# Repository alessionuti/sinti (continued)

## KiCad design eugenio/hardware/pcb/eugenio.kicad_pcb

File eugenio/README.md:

# Eugenio
## Euclidean sequencer
See `manual/` for full documentation.

### Acknowledgements
Inspired by:
- [Tombola](https://modwiggler.com/forum/viewtopic.php?t=45485)'s Euclidean Polyrhythm Generator
- [TimMJN](https://github.com/TimMJN/Arduino-Euclidean-Rhythm-Generator)'s Arduino Euclidean Rhythm Generator

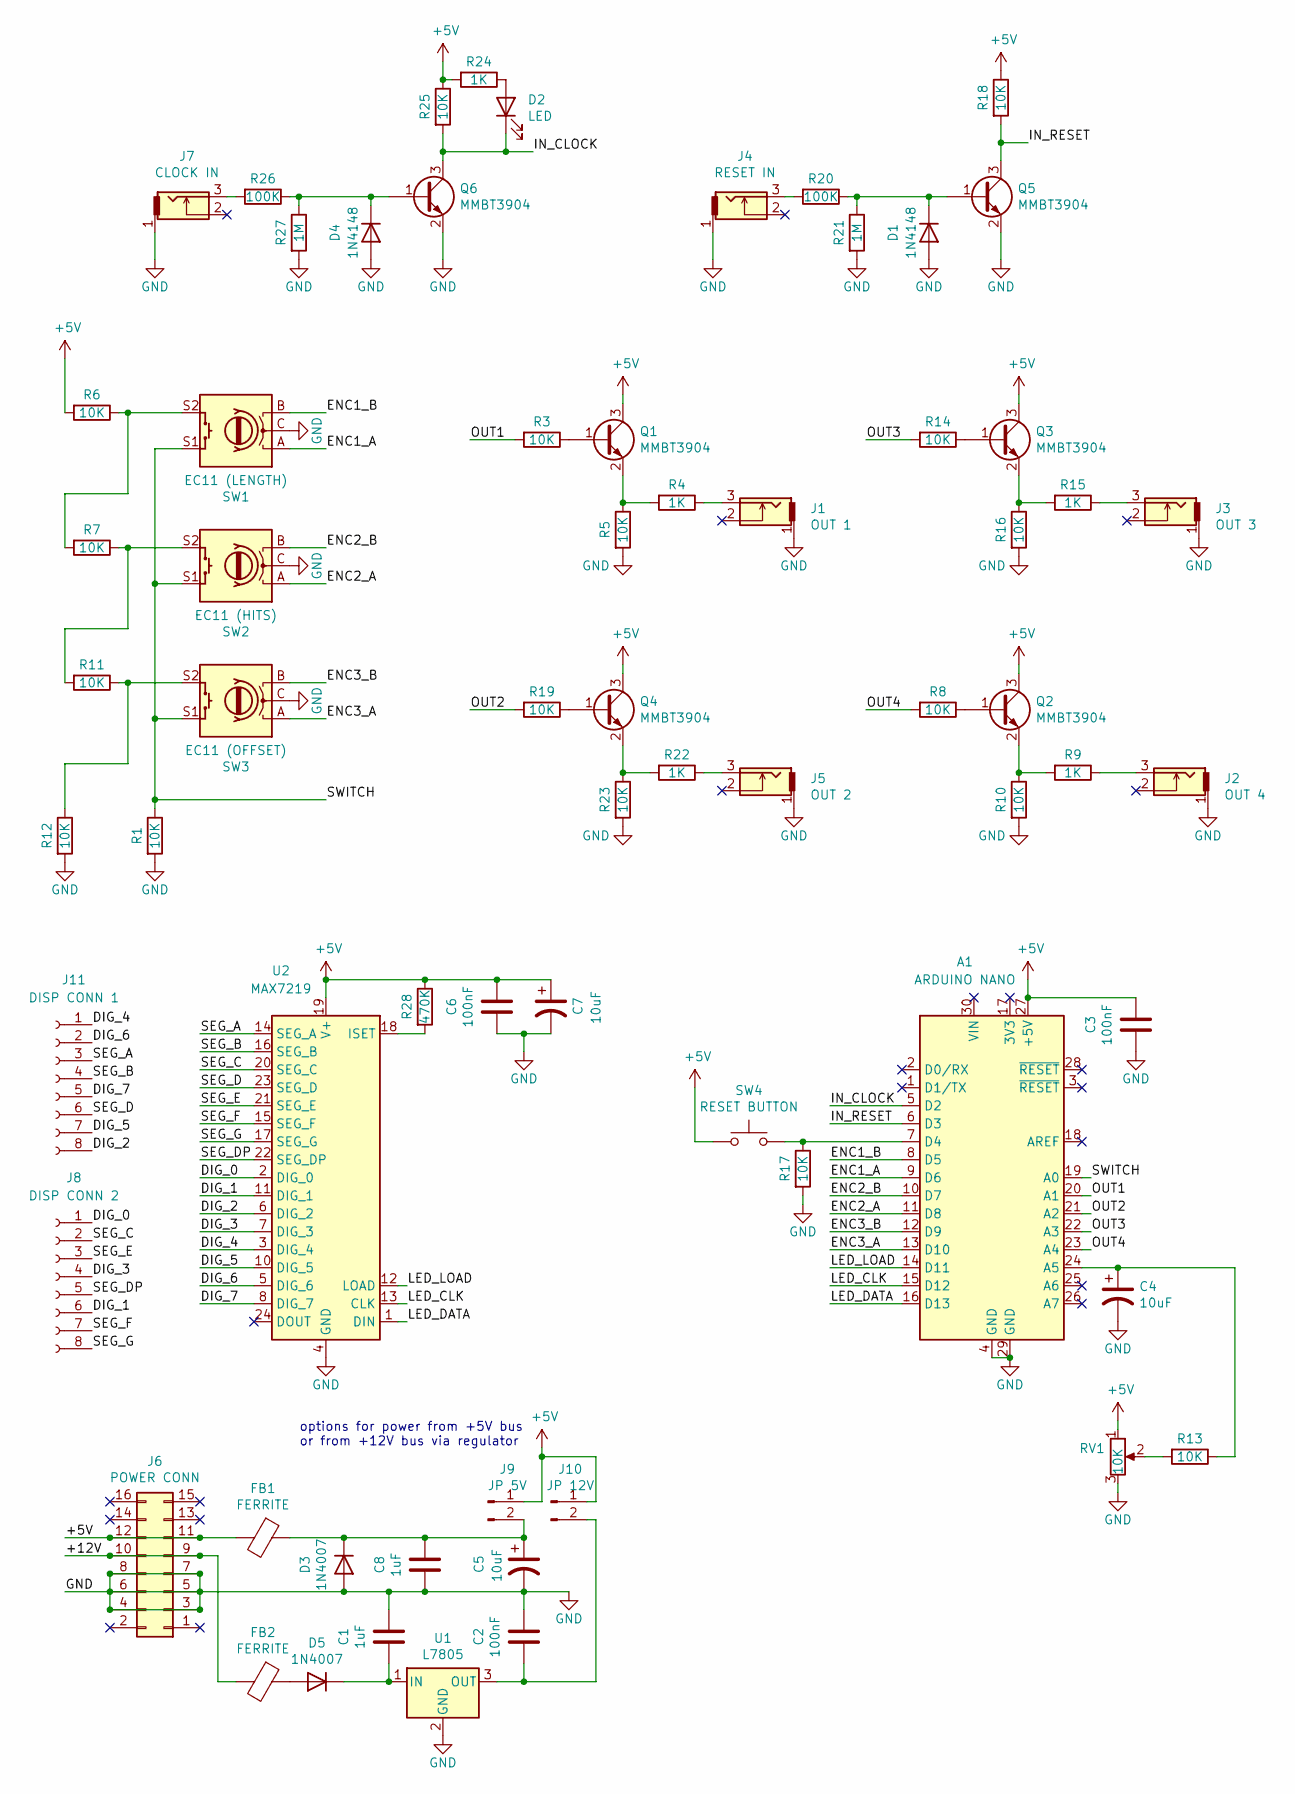
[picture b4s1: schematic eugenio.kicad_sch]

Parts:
A1: ARDUINO NANO; Arduino_Nano
C1, C8: 1uF; C_0805_2012Metric
C2, C3, C6: 100nF; C_0805_2012Metric
C4, C5, C7: 10uF; CP_Elec_5x4.5
D1, D4: 1N4148; D_0805_2012Metric
D2: LED; LED_D3.0mm
D3, D5: 1N4007; D_1206_3216Metric
FB1, FB2: FERRITE; L_0603_1608Metric
J1: OUT 1; THONKICONN
J2: OUT 4; THONKICONN
J3: OUT 3; THONKICONN
J4: RESET IN; THONKICONN
J5: OUT 2; THONKICONN
J6: POWER CONN; IDC-Header_2x08_P2.54mm_Vertical
J7: CLOCK IN; THONKICONN
J8: DISP CONN 2; PinSocket_1x08_P2.54mm_Vertical
J9: JP 5V; SolderJumper-2_P1.3mm_Open_RoundedPad1.0x1.5mm
J10: JP 12V; SolderJumper-2_P1.3mm_Open_RoundedPad1.0x1.5mm
J11: DISP CONN 1; PinSocket_1x08_P2.54mm_Vertical
Q1, Q2, Q3, Q4, Q5, Q6: MMBT3904; SOT-23
R1, R3, R5, R6, R7, R8, R10, R11, R12, R13, R14, R16, R17, R18, R19, R23, R25: 10K; R_0805_2012Metric
R4, R9, R15, R22, R24: 1K; R_0805_2012Metric
R20, R26: 100K; R_0805_2012Metric
R21, R27: 1M; R_0805_2012Metric
R28: 470K; R_0805_2012Metric
RV1: 10K; Potentiometer_Alpha_RD901F-40-00D_Single_Vertical
SW1: EC11 (LENGTH); RotaryEncoder_Alps_EC11E-Switch_Vertical_H20mm
SW2: EC11 (HITS); RotaryEncoder_Alps_EC11E-Switch_Vertical_H20mm
SW3: EC11 (OFFSET); RotaryEncoder_Alps_EC11E-Switch_Vertical_H20mm
SW4: RESET BUTTON; SW_PUSH_6mm
U1: L7805; TO-220-3_Vertical
U2: MAX7219; SOP-24_7.5x15.4mm_P1.27mm

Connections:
+5V: A1.27 (+5V), C3.1, C6.1, C7.1, J9.1, J10.1, Q1.3 (C), Q2.3 (C), Q3.3 (C), Q4.3 (C), R6.2, R18.1, R24.2, R25.1, R28.1, RV1.1, SW4.1, U2.19 (V+)
GND: A1.4 (GND), A1.29 (GND), C1.1, C2.1, C3.2, C4.2, C5.2, C6.2, C7.2, C8.2, D1.2 (A), D3.2 (A), D4.2 (A), J1.1, J2.1, J3.1, J4.1, J5.1, J6.3, J6.4, J6.5, J6.6, J6.7, J6.8, J7.1, Q5.2 (E), Q6.2 (E), R1.2, R5.2, R10.2, R12.2, R16.2, R17.2, R21.2, R23.2, R27.2, RV1.3, SW1.C, SW2.C, SW3.C, U1.2 (GND), U2.4 (GND), U2.9 (GND)
unnamed: A1.5 (D2), D2.1 (K), Q6.3 (C), R25.2
unnamed: A1.6 (D3), Q5.3 (C), R18.2
unnamed: A1.7 (D4), R17.1, SW4.2
unnamed: A1.8 (D5), SW1.B
unnamed: A1.9 (D6), SW1.A
unnamed: A1.10 (D7), SW2.B
unnamed: A1.11 (D8), SW2.A
unnamed: A1.12 (D9), SW3.B
unnamed: A1.13 (D10), SW3.A
unnamed: A1.14 (D11), U2.12 (LOAD)
unnamed: A1.15 (D12), U2.13 (CLK)
unnamed: A1.16 (D13), U2.1 (DIN)
unnamed: A1.19 (A0), R1.1, SW1.S1, SW2.S1, SW3.S1
unnamed: A1.20 (A1), R3.2
unnamed: A1.21 (A2), R19.2
unnamed: A1.22 (A3), R14.2
unnamed: A1.23 (A4), R8.2
unnamed: A1.24 (A5), C4.1, R13.1
unnamed: C1.2, D5.1 (K), U1.1 (IN)
unnamed: C2.2, J10.2, U1.3 (OUT)
unnamed: C5.1, C8.1, D3.1 (K), FB1.1, J9.2
unnamed: D1.1 (K), Q5.1 (B), R20.1, R21.1
unnamed: D2.2 (A), R24.1
unnamed: D4.1 (K), Q6.1 (B), R26.1, R27.1
unnamed: D5.2 (A), FB2.1
unnamed: FB1.2, J6.11, J6.12
unnamed: FB2.2, J6.9, J6.10
unnamed: J1.3, R4.1
unnamed: J2.3, R9.1
unnamed: J3.3, R15.1
unnamed: J4.3, R20.2
unnamed: J5.3, R22.1
unnamed: J7.3, R26.2
unnamed: J8.1, U2.2 (DIG_0)
unnamed: J8.2, U2.20 (SEG_C)
unnamed: J8.3, U2.21 (SEG_E)
unnamed: J8.4, U2.7 (DIG_3)
unnamed: J8.5, U2.22 (SEG_DP)
unnamed: J8.6, U2.11 (DIG_1)
unnamed: J8.7, U2.15 (SEG_F)
unnamed: J8.8, U2.17 (SEG_G)
unnamed: J11.1, U2.3 (DIG_4)
unnamed: J11.2, U2.5 (DIG_6)
unnamed: J11.3, U2.14 (SEG_A)
unnamed: J11.4, U2.16 (SEG_B)
unnamed: J11.5, U2.8 (DIG_7)
unnamed: J11.6, U2.23 (SEG_D)
unnamed: J11.7, U2.10 (DIG_5)
unnamed: J11.8, U2.6 (DIG_2)
unnamed: Q1.1 (B), R3.1
unnamed: Q1.2 (E), R4.2, R5.1
unnamed: Q2.1 (B), R8.1
unnamed: Q2.2 (E), R9.2, R10.1
unnamed: Q3.1 (B), R14.1
unnamed: Q3.2 (E), R15.2, R16.1
unnamed: Q4.1 (B), R19.1
unnamed: Q4.2 (E), R22.2, R23.1
unnamed: R6.1, R7.2, SW1.S2
unnamed: R11.1, R12.1, SW3.S2
unnamed: R7.1, R11.2, SW2.S2
unnamed: R13.2, RV1.2
unnamed: R28.2, U2.18 (ISET)

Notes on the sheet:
options for power from +5V bus or from +12V bus via regulator

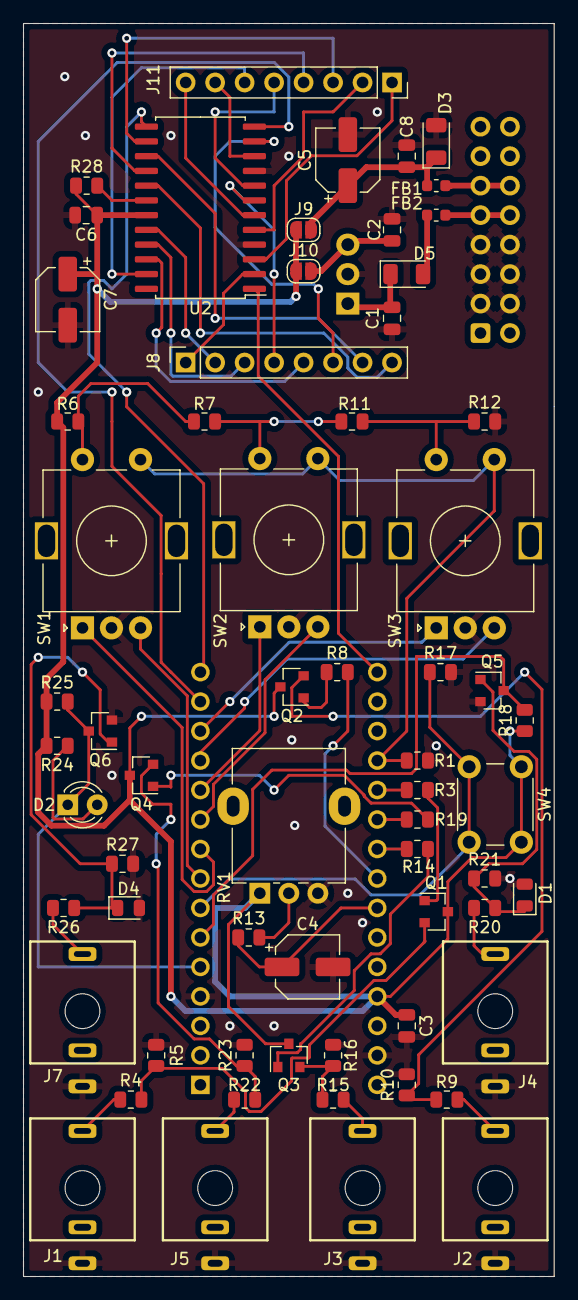
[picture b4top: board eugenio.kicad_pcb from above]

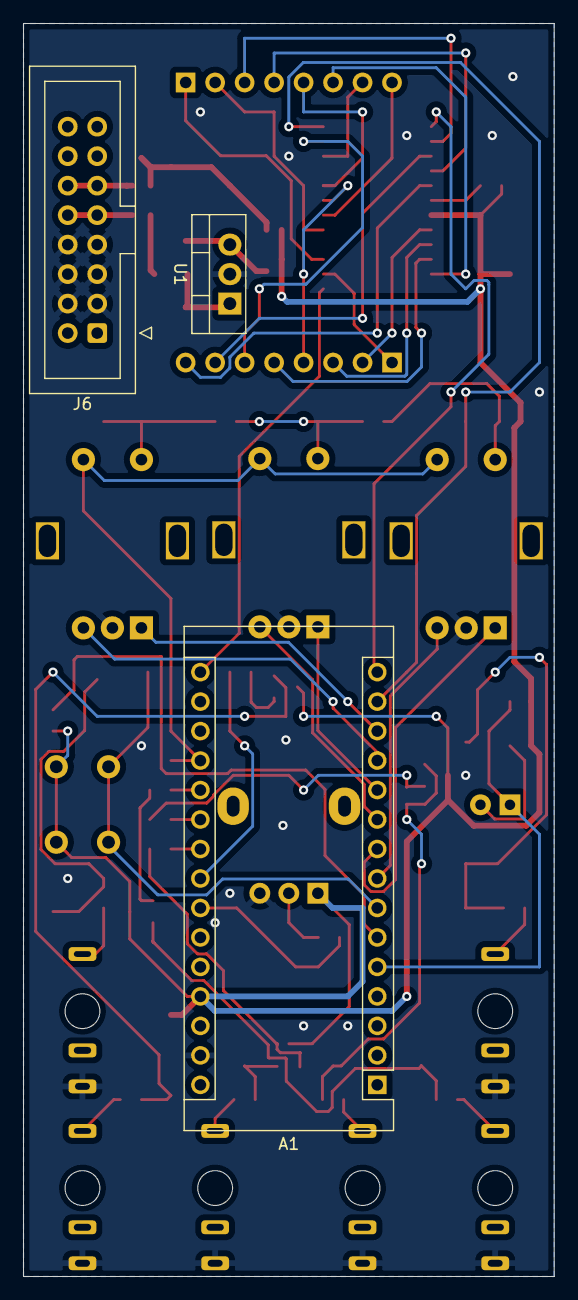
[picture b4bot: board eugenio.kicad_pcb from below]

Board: 2 copper layers, 45.7 x 107.9 mm, 67 parts (3 on the bottom side), 64 nets.

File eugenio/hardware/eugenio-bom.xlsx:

Qty | Reference(s) | Value | Footprint
1 | A1 | ARDUINO NANO | Arduino Nano Module
2 | C1, C8 | 1uF | Capacitor SMD 0805
3 | C2, C3, C6 | 100nF | Capacitor SMD 0805
3 | C4, C5, C7 | 10uF | Capacitor SMD Elec 5x4.5
2 | D1, D4 | 1N4148 | Diode SMD 0805
1 | D2 | LED | LED THT 3.0mm
2 | D3, D5 | 1N4007 | Diode SMD 1206
2 | FB1, FB2 | FERRITE | Ferrite Bead SMD 0603
1 | J1 | OUT 1 | Thonkiconn Jack
1 | J2 | OUT 4 | Thonkiconn Jack
1 | J3 | OUT 3 | Thonkiconn Jack
1 | J4 | RESET IN | Thonkiconn Jack
1 | J5 | OUT 2 | Thonkiconn Jack
1 | J6 | POWER CONN | Pin header 2x8
1 | J7 | CLOCK IN | Thonkiconn Jack
1 | J8 | DISP CONN 2 | Pin socket 1x8
1 | J9 | JP 5V | Solder Jumper
1 | J10 | JP 12V | Solder Jumper
1 | J11 | DISP CONN 1 | Pin socket 1x8
6 | Q1, Q2, Q3, Q4, Q5, Q6 | MMBT3904 | Transistor SMD SOT-23
17 | R1, R3, R5, R6, R7, R8, R10, R11, R12, R13, R14, R16, R17, R18, R19, R23, R25 | 10K | Resistor SMD 0805
5 | R4, R9, R15, R22, R24 | 1K | Resistor SMD 0805
2 | R20, R26 | 100K | Resistor SMD 0805
2 | R21, R27 | 1M | Resistor SMD 0805
1 | R28 | 470K | Resistor SMD 0805
1 | RV1 | 10K | Potentiometer THT Single Vertical
1 | SW1 | EC11 (LENGTH) | Rotary Encoder Alps EC11 Switch Vertical
1 | SW2 | EC11 (HITS) | Rotary Encoder Alps EC11 Switch Vertical
1 | SW3 | EC11 (OFFSET) | Rotary Encoder Alps EC11 Switch Vertical
1 | SW4 | RESET BUTTON | Button Switch THT 6mm
1 | U1 | L7805 | Voltage Regulator THT TO-220
1 | U2 | MAX7219/MAX7221 | Led Controller SMD SOP-24

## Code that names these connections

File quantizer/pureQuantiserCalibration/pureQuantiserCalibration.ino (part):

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#include "SPI.h"

//Setup LED Pin Varibles
const byte LR_0 = A3;
const byte LR_1 = A4;
const byte LR_2 = A5;
const byte LR_3 = 7;
const byte LC_0 = A0;
const byte LC_1 = A1;
const byte LC_2 = A2;

//Setup Button Pin Variables
const byte BC_0 = 2;
const byte BC_1 = 1;
const byte BC_2 = 0;
const byte BR_0 = 3;
const byte BR_1 = 4;
const byte BR_2 = 5;
const byte BR_3 = 6;

//Setup variable for the notes
int notes[12] = {0, 0, 0, 0, 0, 0, 0, 0, 0, 0, 0, 0};
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const byte CS_DAC = 10;

//Setup CV and Trigger Pin Variables
const byte TRIG = 8;
int cvIn;
int cvOut;

void setup() {
    //Setup LED Pins
    pinMode(LR_0, OUTPUT);
    pinMode(LR_1, OUTPUT);
    pinMode(LR_2, OUTPUT);
    pinMode(LR_3, OUTPUT);
    pinMode(LC_0, OUTPUT);
    pinMode(LC_1, OUTPUT);
    pinMode(LC_2, OUTPUT);

    digitalWrite(LR_0, HIGH);
    digitalWrite(LR_1, HIGH);
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    digitalWrite(LC_2, LOW);

    //Setup Button Pins
    pinMode(BC_0, OUTPUT);
    pinMode(BC_1, OUTPUT);
    pinMode(BC_2, OUTPUT);
    pinMode(BR_0, INPUT);
    pinMode(BR_1, INPUT);
    pinMode(BR_2, INPUT);
    pinMode(BR_3, INPUT);

    digitalWrite(BC_0, LOW);
    digitalWrite(BC_1, LOW);
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    SPI.begin();

    //Setup Trigger Pin
    pinMode(TRIG, OUTPUT);
    digitalWrite(TRIG, LOW);
}

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
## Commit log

2021-11-11 adsr code
2021-11-12 quantizer + fix envelope
2021-11-13 new quantization function
2021-11-14 fixed quantizer
2021-11-19 release quantizer 1.0
2021-12-02 eugene first commit
2021-12-03 eugene fixes
2021-12-03 fix reset logic&pulse length
2022-01-23 major update eugene
2022-02-03 bug fixes
2022-02-03 renamed eugenio
2022-03-09 new schematic, internal clock and pulse length
2022-06-13 corrections for pcb version
2022-10-17 update display
2022-11-20 updated firmware, pcb, manual
2023-04-14 refactored projects
2023-06-17 version 4.0 beta1 quanti
2023-06-29 quanto 4.0
2023-07-05 release
2024-09-17 fixed eugenio encoder reading bug
